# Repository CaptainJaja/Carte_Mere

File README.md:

# Carte mère – Coupe de France de Robotique

> Carte mère basée sur un **STM32H5** en boîtier **LQFP177**.  
> Conçue pour centraliser la communication et le pilotage des modules du robot, avec une connectique optimisée pour la robustesse et la modularité.

---

## Caractéristiques principales

- **Microcontrôleur** : STM32H5, LQFP177  
- **Interfaces série** : 12 UARTs, chacun exposé sur connecteurs **VCC – GND – TX – GND – RX** afin de permettre le torsadage avec un retour GND pour une meilleure intégrité du signal  
- **Bus I²C** : 3 bus indépendants, jusqu’à **13 connexions** possibles (chaque connecteur fournit 2 GPIOs, GND et 3V3)  
- **Convertisseurs analogiques (ADC)** : 12 entrées, rangées avec alimentation 3V3 et GND pour faciliter le câblage  
- **USB-C** : un connecteur intégré pour programmation et alimentation  
- **Timers** : 12 broches disponibles pour PWM et capture/compare  
- **GPIO** : 10 broches générales, chacune associée à GND et 3V3 pour plus de flexibilité  
- **SPI** : 4 full duplex master, avec chacun des broches power et deux gpios 

---

## Vues du PCB

### Face composants

### Face cuivre arrière

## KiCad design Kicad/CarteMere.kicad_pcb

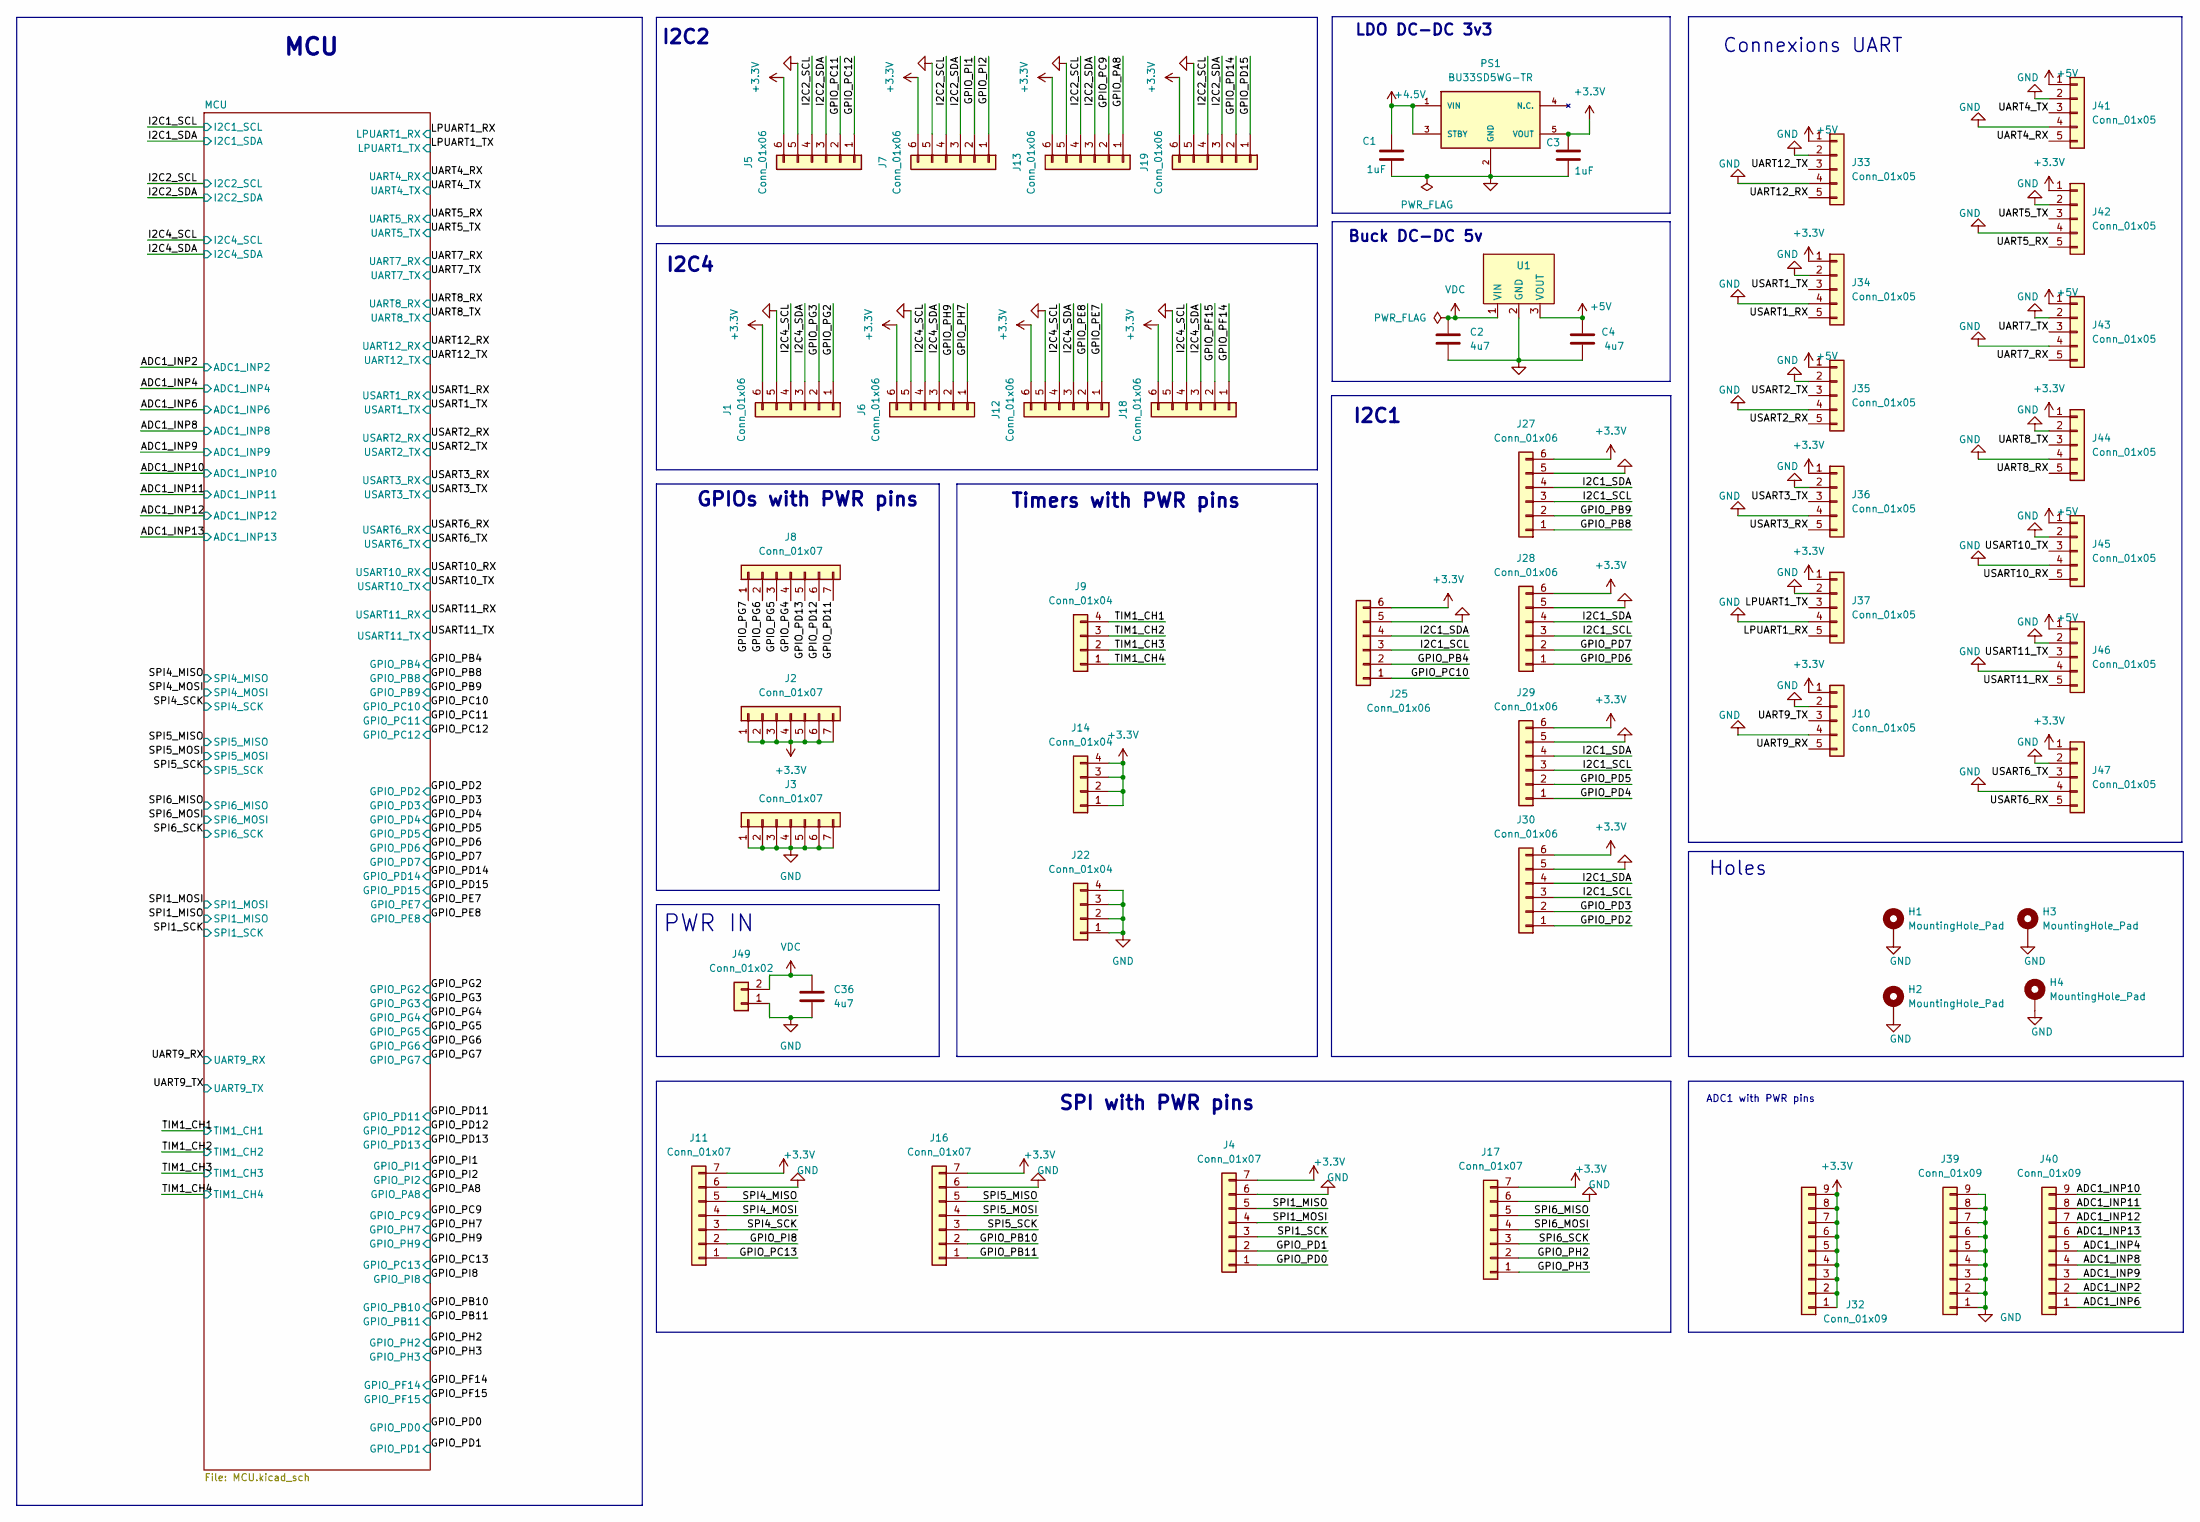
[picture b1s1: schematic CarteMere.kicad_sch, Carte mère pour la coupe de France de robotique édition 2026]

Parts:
C1, C3: 1uF; C_0603_1608Metric
C2: 4u7; C_1206_3216Metric
C4: 4u7; C_0603_1608Metric
C36: 4u7; C_0805_2012Metric
H1, H2, H3, H4: MountingHole_Pad; MountingHole_2.2mm_M2_Pad
J1, J5, J6, J7, J12, J13, J18, J19, J25, J27, J28, J29, J30: Conn_01x06; JST_EH_B6B-EH-A_1x06_P2.50mm_Vertical
J2, J3, J8: Conn_01x07; PinHeader_1x07_P2.54mm_Vertical
J4, J11, J16, J17: Conn_01x07; JST_EH_B7B-EH-A_1x07_P2.50mm_Vertical
J9, J14, J22: Conn_01x04; PinHeader_1x04_P2.54mm_Vertical
J10, J33, J34, J35, J36, J37, J41, J42, J43, J44, J45, J46, J47: Conn_01x05; JST_EH_B5B-EH-A_1x05_P2.50mm_Vertical
J32, J39, J40: Conn_01x09; PinHeader_1x09_P2.54mm_Vertical
J49: Conn_01x02; KF301-5.0-2P
PS1: BU33SD5WG-TR; SOT95P280X125-5N; Mouser_Part_Number 755-BU33SD5WG-TR
U1: StepDown3v3; MPN 173010x78

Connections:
+3.3V: C3.1, J1.6, J2.1, J2.2, J2.3, J2.4, J2.5, J2.6, J2.7, J4.7, J5.6, J6.6, J7.6, J10.1, J11.7, J12.6, J13.6, J14.1, J14.2, J14.3, J14.4, J16.7, J17.7, J18.6, J19.6, J25.6, J27.6, J28.6, J29.6, J30.6, J32.1, J32.2, J32.3, J32.4, J32.5, J32.6, J32.7, J32.8, J32.9, J34.1, J36.1, J37.1, J42.1, J44.1, J47.1, PS1.5 (VOUT); also elsewhere on the board
+4.5V: C1.1, PS1.1 (VIN), PS1.3 (STBY); also elsewhere on the board
+5V: C4.1, J33.1, J35.1, J41.1, J43.1, J45.1, J46.1, U1.3 (VOUT); also elsewhere on the board
/ADC1_INP2: J40.2; also elsewhere on the board
/ADC1_INP4: J40.5; also elsewhere on the board
/ADC1_INP6: J40.1; also elsewhere on the board
/ADC1_INP8: J40.4; also elsewhere on the board
/ADC1_INP9: J40.3; also elsewhere on the board
/ADC1_INP10: J40.9; also elsewhere on the board
/ADC1_INP11: J40.8; also elsewhere on the board
/ADC1_INP12: J40.7; also elsewhere on the board
/ADC1_INP13: J40.6; also elsewhere on the board
/GPIO_PA8: J13.1; also elsewhere on the board
/GPIO_PB4: J25.2; also elsewhere on the board
/GPIO_PB8: J27.1; also elsewhere on the board
/GPIO_PB9: J27.2; also elsewhere on the board
/GPIO_PB10: J16.2; also elsewhere on the board
/GPIO_PB11: J16.1; also elsewhere on the board
/GPIO_PC9: J13.2; also elsewhere on the board
/GPIO_PC10: J25.1; also elsewhere on the board
/GPIO_PC11: J5.2; also elsewhere on the board
/GPIO_PC12: J5.1; also elsewhere on the board
/GPIO_PC13: J11.1; also elsewhere on the board
/GPIO_PD0: J4.1; also elsewhere on the board
/GPIO_PD1: J4.2; also elsewhere on the board
/GPIO_PD2: J30.1; also elsewhere on the board
/GPIO_PD3: J30.2; also elsewhere on the board
/GPIO_PD4: J29.1; also elsewhere on the board
/GPIO_PD5: J29.2; also elsewhere on the board
/GPIO_PD6: J28.1; also elsewhere on the board
/GPIO_PD7: J28.2; also elsewhere on the board
/GPIO_PD11: J8.7; also elsewhere on the board
/GPIO_PD12: J8.6; also elsewhere on the board
/GPIO_PD13: J8.5; also elsewhere on the board
/GPIO_PD14: J19.2; also elsewhere on the board
/GPIO_PD15: J19.1; also elsewhere on the board
/GPIO_PE7: J12.1; also elsewhere on the board
/GPIO_PE8: J12.2; also elsewhere on the board
/GPIO_PF14: J18.1; also elsewhere on the board
/GPIO_PF15: J18.2; also elsewhere on the board
/GPIO_PG2: J1.1; also elsewhere on the board
/GPIO_PG3: J1.2; also elsewhere on the board
/GPIO_PG4: J8.4; also elsewhere on the board
/GPIO_PG5: J8.3; also elsewhere on the board
/GPIO_PG6: J8.2; also elsewhere on the board
/GPIO_PG7: J8.1; also elsewhere on the board
/GPIO_PH2: J17.2; also elsewhere on the board
/GPIO_PH3: J17.1; also elsewhere on the board
/GPIO_PH7: J6.1; also elsewhere on the board
/GPIO_PH9: J6.2; also elsewhere on the board
/GPIO_PI1: J7.2; also elsewhere on the board
/GPIO_PI2: J7.1; also elsewhere on the board
/GPIO_PI8: J11.2; also elsewhere on the board
/I2C1_SCL: J25.3, J27.3, J28.3, J29.3, J30.3; also elsewhere on the board
/I2C1_SDA: J25.4, J27.4, J28.4, J29.4, J30.4; also elsewhere on the board
/I2C2_SCL: J5.4, J7.4, J13.4, J19.4; also elsewhere on the board
/I2C2_SDA: J5.3, J7.3, J13.3, J19.3; also elsewhere on the board
/I2C4_SCL: J1.4, J6.4, J12.4, J18.4; also elsewhere on the board
/I2C4_SDA: J1.3, J6.3, J12.3, J18.3; also elsewhere on the board
/LPUART1_RX: J37.5; also elsewhere on the board
/LPUART1_TX: J37.3; also elsewhere on the board
/SPI1_MISO: J4.5; also elsewhere on the board
/SPI1_MOSI: J4.4; also elsewhere on the board
/SPI1_SCK: J4.3; also elsewhere on the board
/SPI4_MISO: J11.5; also elsewhere on the board
/SPI4_MOSI: J11.4; also elsewhere on the board
/SPI4_SCK: J11.3; also elsewhere on the board
/SPI5_MISO: J16.5; also elsewhere on the board
/SPI5_MOSI: J16.4; also elsewhere on the board
/SPI5_SCK: J16.3; also elsewhere on the board
/SPI6_MISO: J17.5; also elsewhere on the board
/SPI6_MOSI: J17.4; also elsewhere on the board
/SPI6_SCK: J17.3; also elsewhere on the board
/TIM1_CH1: J9.4; also elsewhere on the board
/TIM1_CH2: J9.3; also elsewhere on the board
/TIM1_CH3: J9.2; also elsewhere on the board
/TIM1_CH4: J9.1; also elsewhere on the board
/UART4_RX: J41.5; also elsewhere on the board
/UART4_TX: J41.3; also elsewhere on the board
/UART5_RX: J42.5; also elsewhere on the board
/UART5_TX: J42.3; also elsewhere on the board
/UART7_RX: J43.5; also elsewhere on the board
/UART7_TX: J43.3; also elsewhere on the board
/UART8_RX: J44.5; also elsewhere on the board
/UART8_TX: J44.3; also elsewhere on the board
/UART9_RX: J10.5; also elsewhere on the board
/UART9_TX: J10.3; also elsewhere on the board
/UART12_RX: J33.5; also elsewhere on the board
/UART12_TX: J33.3; also elsewhere on the board
/USART1_RX: J34.5; also elsewhere on the board
/USART1_TX: J34.3; also elsewhere on the board
/USART2_RX: J35.5; also elsewhere on the board
/USART2_TX: J35.3; also elsewhere on the board
/USART3_RX: J36.5; also elsewhere on the board
/USART3_TX: J36.3; also elsewhere on the board
/USART6_RX: J47.5; also elsewhere on the board
/USART6_TX: J47.3; also elsewhere on the board
/USART10_RX: J45.5; also elsewhere on the board
/USART10_TX: J45.3; also elsewhere on the board
/USART11_RX: J46.5; also elsewhere on the board
/USART11_TX: J46.3; also elsewhere on the board
GND: C1.2, C2.2, C3.2, C4.2, C36.2, H1.1, H2.1, H3.1, H4.1, J1.5, J3.1, J3.2, J3.3, J3.4, J3.5, J3.6, J3.7, J4.6, J5.5, J6.5, J7.5, J10.2, J10.4, J11.6, J12.5, J13.5, J16.6, J17.6, J18.5, J19.5, J22.1, J22.2, J22.3, J22.4, J25.5, J27.5, J28.5, J29.5, J30.5, J33.2, J33.4, J34.2, J34.4, J35.2, J35.4, J36.2, J36.4, J37.2, J37.4, J39.1, J39.2, J39.3, J39.4, J39.5, J39.6, J39.7, J39.8, J39.9, J41.2, J41.4, J42.2, J42.4, J43.2, J43.4, J44.2, J44.4, J45.2, J45.4, J46.2, J46.4, J47.2, J47.4, J49.1, PS1.2 (GND), U1.2 (GND); also elsewhere on the board
VDC: C2.1, C36.1, J49.2, U1.1 (VIN)

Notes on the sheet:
SPI with PWR pins
I2C2
MCU
PWR IN
I2C4
Connexions UART
Buck DC-DC 5v
LDO DC-DC 3v3
GPIOs with PWR pins
Timers with PWR pins
I2C1
ADC1 with PWR pins
Holes

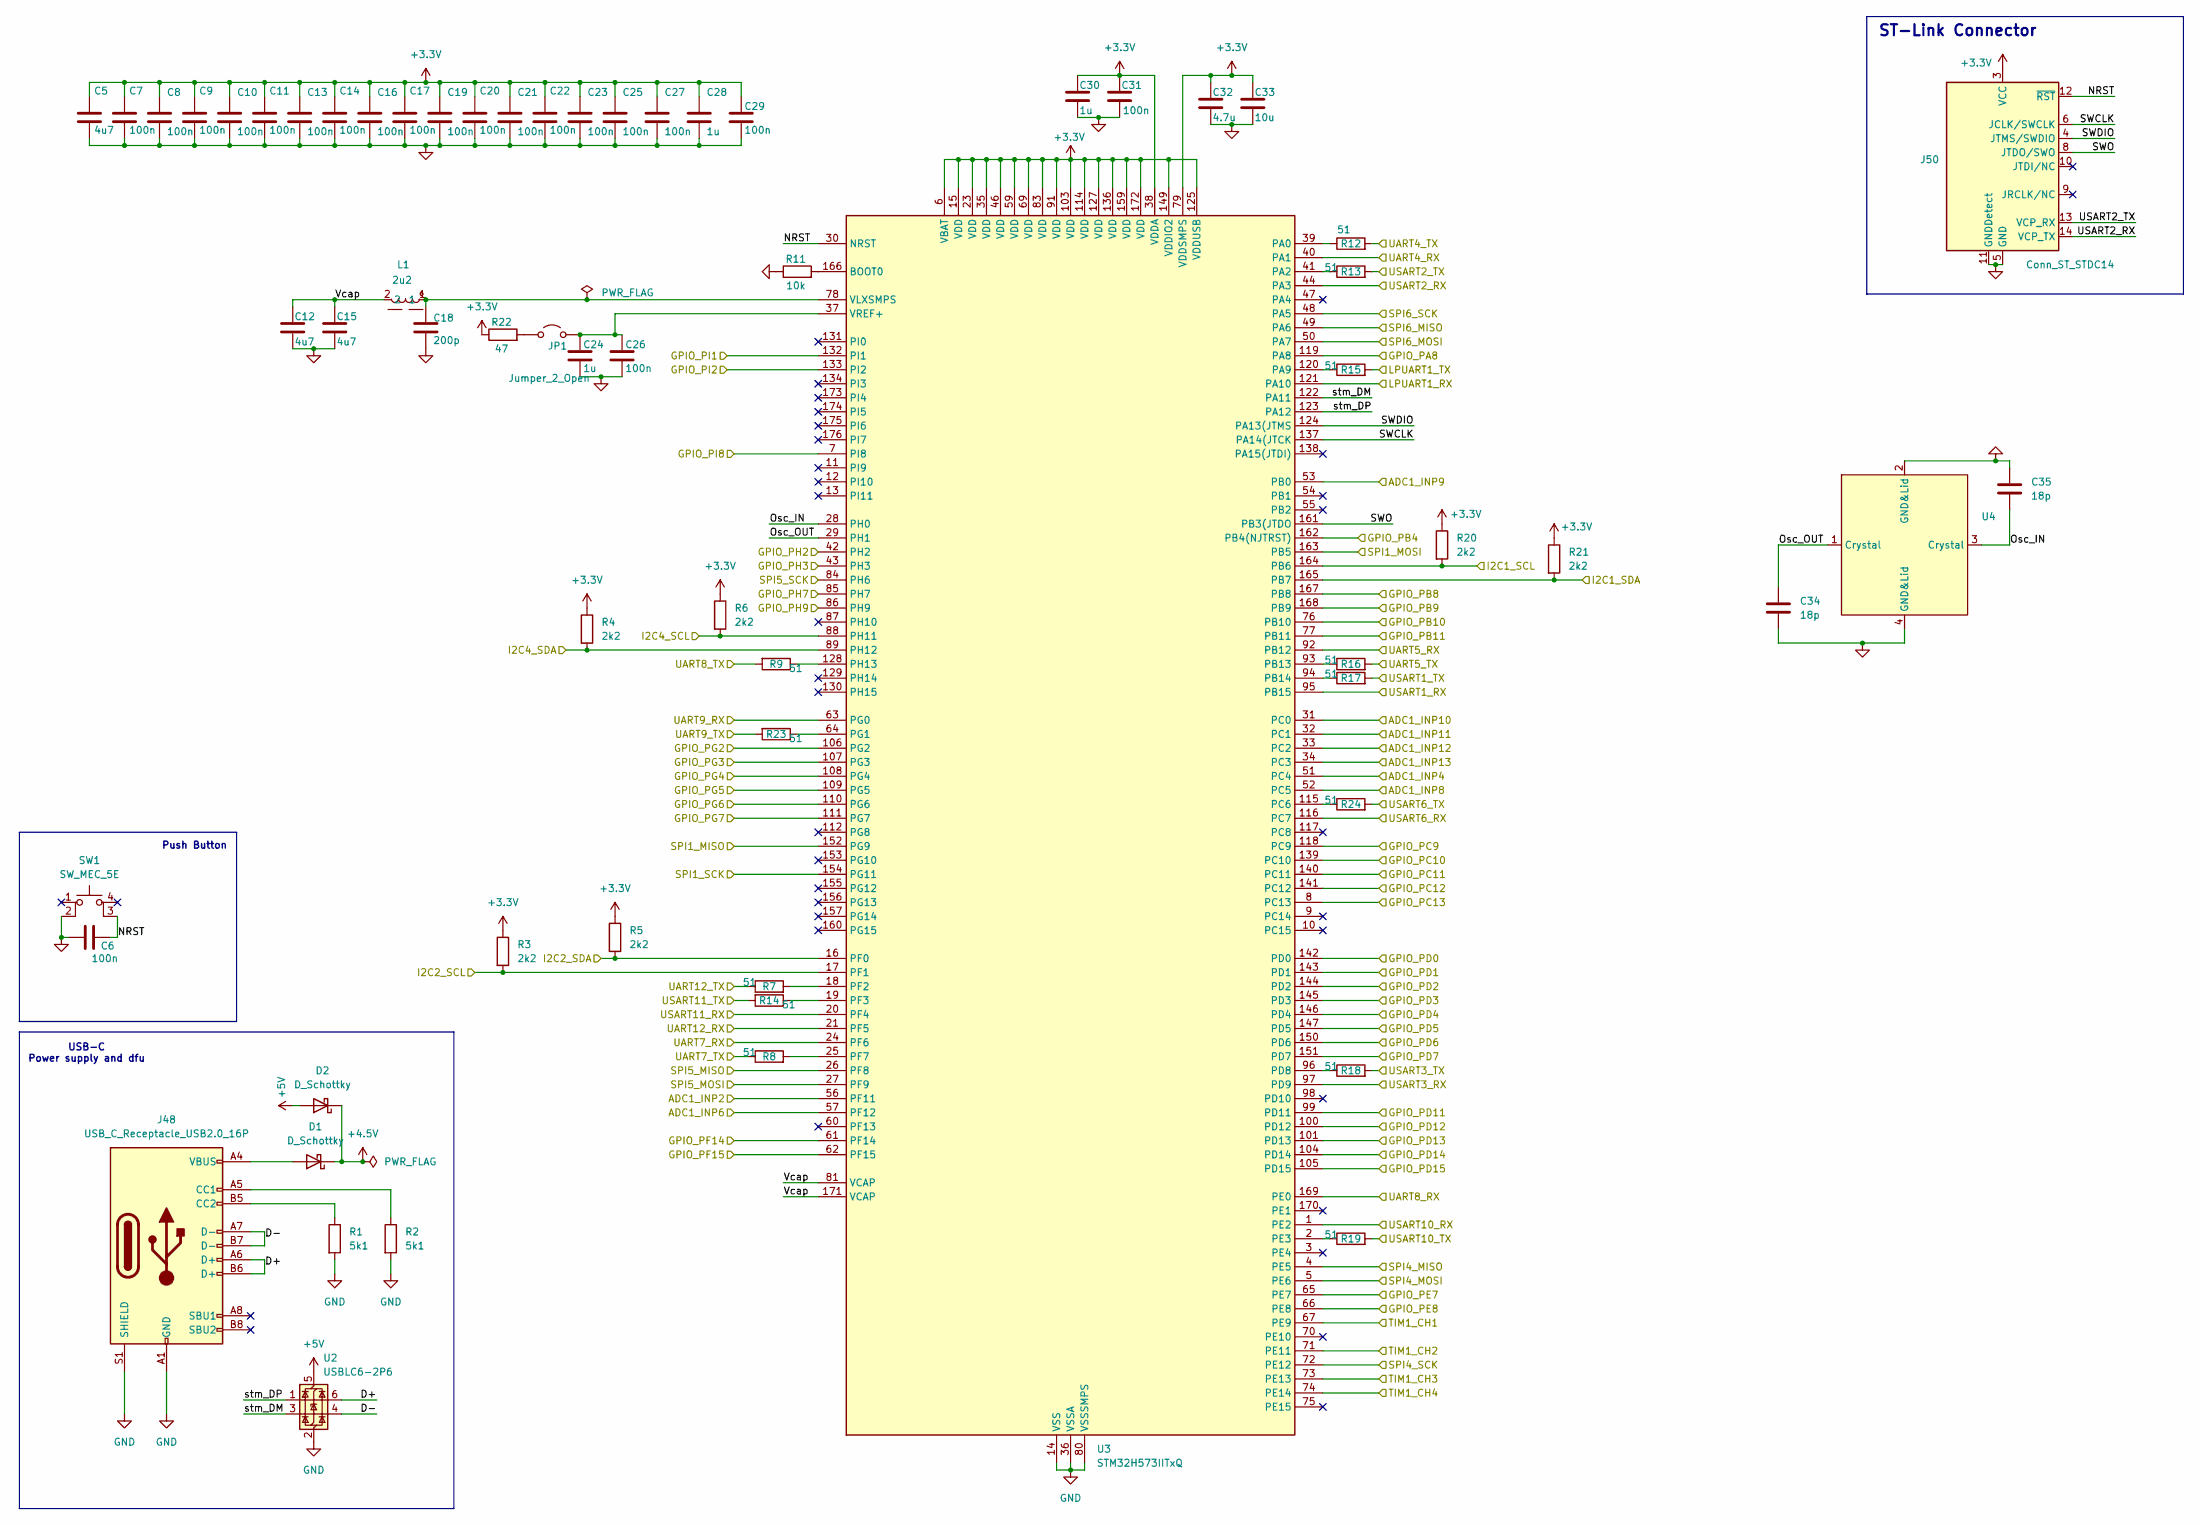
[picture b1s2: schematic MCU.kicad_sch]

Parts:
C5, C12, C15: 4u7; C_0402_1005Metric
C6, C7, C8, C9, C10, C11, C13, C14, C16, C17, C19, C20, C21, C22, C23, C25, C26, C27, C29, C31: 100n; C_0402_1005Metric
C18: 200p; C_0402_1005Metric
C24, C28, C30: 1u; C_0402_1005Metric
C32: 4.7u; C_0402_1005Metric
C33: 10u; C_0402_1005Metric
C34, C35: 18p; C_0603_1608Metric
D1, D2: D_Schottky; D_SMA
J48: USB_C_Receptacle_USB2.0_16P; USB_C_Receptacle_HRO_TYPE-C-31-M-12
J50: Conn_ST_STDC14; PinHeader_2x07_P1.27mm_Vertical_SMD
JP1: Jumper_2_Open; PinHeader_1x02_P2.54mm_Vertical
L1: 2u2; 7440660022
R1, R2: 5k1; R_0402_1005Metric
R3, R4, R5, R6, R20, R21: 2k2; R_0402_1005Metric
R7, R8, R9, R12, R13, R14, R15, R16, R17, R18, R19, R23, R24: 51; R_0402_1005Metric
R11: 10k; R_0402_1005Metric
R22: 47; R_0402_1005Metric
SW1: SW_MEC_5E; WS-TASU SMT Tact Switch 4.7x3.5 mm side push
U2: USBLC6-2P6; SOT-666
U3: STM32H573IITxQ; LQFP-176_24x24mm_P0.5mm
U4: WE-XTAL Quartz Crystal 8MHz

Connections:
+3.3V: C5.1, C7.1, C8.1, C9.1, C10.1, C11.1, C13.1, C14.1, C16.1, C17.1, C19.1, C20.1, C21.1, C22.1, C23.1, C25.1, C27.1, C28.1, C29.1, C30.1, C31.1, C32.1, C33.1, J50.3 (VCC), R3.1, R4.1, R5.1, R6.1, R20.1, R21.1, R22.1, U3.6 (VBAT), U3.15 (VDD), U3.23 (VDD), U3.35 (VDD), U3.38 (VDDA), U3.46 (VDD), U3.59 (VDD), U3.69 (VDD), U3.79 (VDDSMPS), U3.83 (VDD), U3.91 (VDD), U3.103 (VDD), U3.114 (VDD), U3.125 (VDDUSB), U3.127 (VDD), U3.136 (VDD), U3.149 (VDDIO2), U3.159 (VDD), U3.172 (VDD); also elsewhere on the board
+4.5V: D1.1 (K), D2.1 (K); also elsewhere on the board
+5V: D2.2 (A), U2.5 (VBUS); also elsewhere on the board
/ADC1_INP2: U3.56 (PF11); also elsewhere on the board
/ADC1_INP4: U3.51 (PC4); also elsewhere on the board
/ADC1_INP6: U3.57 (PF12); also elsewhere on the board
/ADC1_INP8: U3.52 (PC5); also elsewhere on the board
/ADC1_INP9: U3.53 (PB0); also elsewhere on the board
/ADC1_INP10: U3.31 (PC0); also elsewhere on the board
/ADC1_INP11: U3.32 (PC1); also elsewhere on the board
/ADC1_INP12: U3.33 (PC2); also elsewhere on the board
/ADC1_INP13: U3.34 (PC3); also elsewhere on the board
/GPIO_PA8: U3.119 (PA8); also elsewhere on the board
/GPIO_PB4: U3.162 (PB4(NJTRST)); also elsewhere on the board
/GPIO_PB8: U3.167 (PB8); also elsewhere on the board
/GPIO_PB9: U3.168 (PB9); also elsewhere on the board
/GPIO_PB10: U3.76 (PB10); also elsewhere on the board
/GPIO_PB11: U3.77 (PB11); also elsewhere on the board
/GPIO_PC9: U3.118 (PC9); also elsewhere on the board
/GPIO_PC10: U3.139 (PC10); also elsewhere on the board
/GPIO_PC11: U3.140 (PC11); also elsewhere on the board
/GPIO_PC12: U3.141 (PC12); also elsewhere on the board
/GPIO_PC13: U3.8 (PC13); also elsewhere on the board
/GPIO_PD0: U3.142 (PD0); also elsewhere on the board
/GPIO_PD1: U3.143 (PD1); also elsewhere on the board
/GPIO_PD2: U3.144 (PD2); also elsewhere on the board
/GPIO_PD3: U3.145 (PD3); also elsewhere on the board
/GPIO_PD4: U3.146 (PD4); also elsewhere on the board
/GPIO_PD5: U3.147 (PD5); also elsewhere on the board
/GPIO_PD6: U3.150 (PD6); also elsewhere on the board
/GPIO_PD7: U3.151 (PD7); also elsewhere on the board
/GPIO_PD11: U3.99 (PD11); also elsewhere on the board
/GPIO_PD12: U3.100 (PD12); also elsewhere on the board
/GPIO_PD13: U3.101 (PD13); also elsewhere on the board
/GPIO_PD14: U3.104 (PD14); also elsewhere on the board
/GPIO_PD15: U3.105 (PD15); also elsewhere on the board
/GPIO_PE7: U3.65 (PE7); also elsewhere on the board
/GPIO_PE8: U3.66 (PE8); also elsewhere on the board
/GPIO_PF14: U3.61 (PF14); also elsewhere on the board
/GPIO_PF15: U3.62 (PF15); also elsewhere on the board
/GPIO_PG2: U3.106 (PG2); also elsewhere on the board
/GPIO_PG3: U3.107 (PG3); also elsewhere on the board
/GPIO_PG4: U3.108 (PG4); also elsewhere on the board
/GPIO_PG5: U3.109 (PG5); also elsewhere on the board
/GPIO_PG6: U3.110 (PG6); also elsewhere on the board
/GPIO_PG7: U3.111 (PG7); also elsewhere on the board
/GPIO_PH2: U3.42 (PH2); also elsewhere on the board
/GPIO_PH3: U3.43 (PH3); also elsewhere on the board
/GPIO_PH7: U3.85 (PH7); also elsewhere on the board
/GPIO_PH9: U3.86 (PH9); also elsewhere on the board
/GPIO_PI1: U3.132 (PI1); also elsewhere on the board
/GPIO_PI2: U3.133 (PI2); also elsewhere on the board
/GPIO_PI8: U3.7 (PI8); also elsewhere on the board
/I2C1_SCL: R20.2, U3.164 (PB6); also elsewhere on the board
/I2C1_SDA: R21.2, U3.165 (PB7); also elsewhere on the board
/I2C2_SCL: R3.2, U3.17 (PF1); also elsewhere on the board
/I2C2_SDA: R5.2, U3.16 (PF0); also elsewhere on the board
/I2C4_SCL: R6.2, U3.88 (PH11); also elsewhere on the board
/I2C4_SDA: R4.2, U3.89 (PH12); also elsewhere on the board
/LPUART1_RX: U3.121 (PA10); also elsewhere on the board
/LPUART1_TX: R15.2; also elsewhere on the board
/MCU/D+: J48.A6 (D+), J48.B6 (D+), U2.6 (I/O1)
/MCU/D-: J48.A7 (D-), J48.B7 (D-), U2.4 (I/O2)
/MCU/NRST: C6.2, J50.12 (~RST), SW1.3 (K), U3.30 (NRST)
/MCU/Osc_IN: C35.2, U3.28 (PH0), U4.3 (Crystal)
/MCU/Osc_OUT: C34.1, U3.29 (PH1), U4.1 (Crystal)
/MCU/SWCLK: J50.6 (JCLK/SWCLK), U3.137 (PA14(JTCK)
/MCU/SWDIO: J50.4 (JTMS/SWDIO), U3.124 (PA13(JTMS)
/MCU/SWO: J50.8 (JTDO/SWO), U3.161 (PB3(JTDO)
/MCU/Vcap: C12.1, C15.1, L1.2, U3.81 (VCAP), U3.171 (VCAP)
/MCU/stm_DM: U2.3 (I/O2), U3.122 (PA11)
/MCU/stm_DP: U2.1 (I/O1), U3.123 (PA12)
/SPI1_MISO: U3.152 (PG9); also elsewhere on the board
/SPI1_MOSI: U3.163 (PB5); also elsewhere on the board
/SPI1_SCK: U3.154 (PG11); also elsewhere on the board
/SPI4_MISO: U3.4 (PE5); also elsewhere on the board
/SPI4_MOSI: U3.5 (PE6); also elsewhere on the board
/SPI4_SCK: U3.72 (PE12); also elsewhere on the board
/SPI5_MISO: U3.26 (PF8); also elsewhere on the board
/SPI5_MOSI: U3.27 (PF9); also elsewhere on the board
/SPI5_SCK: U3.84 (PH6); also elsewhere on the board
/SPI6_MISO: U3.49 (PA6); also elsewhere on the board
/SPI6_MOSI: U3.50 (PA7); also elsewhere on the board
/SPI6_SCK: U3.48 (PA5); also elsewhere on the board
/TIM1_CH1: U3.67 (PE9); also elsewhere on the board
/TIM1_CH2: U3.71 (PE11); also elsewhere on the board
/TIM1_CH3: U3.73 (PE13); also elsewhere on the board
/TIM1_CH4: U3.74 (PE14); also elsewhere on the board
/UART4_RX: U3.40 (PA1); also elsewhere on the board
/UART4_TX: R12.2; also elsewhere on the board
/UART5_RX: U3.92 (PB12); also elsewhere on the board
/UART5_TX: R16.2; also elsewhere on the board
/UART7_RX: U3.24 (PF6); also elsewhere on the board
/UART7_TX: R8.1; also elsewhere on the board
/UART8_RX: U3.169 (PE0); also elsewhere on the board
/UART8_TX: R9.2; also elsewhere on the board
/UART9_RX: U3.63 (PG0); also elsewhere on the board
/UART9_TX: R23.2; also elsewhere on the board
/UART12_RX: U3.21 (PF5); also elsewhere on the board
/UART12_TX: R7.1; also elsewhere on the board
/USART1_RX: U3.95 (PB15); also elsewhere on the board
/USART1_TX: R17.2; also elsewhere on the board
/USART2_RX: J50.14 (VCP_TX), U3.44 (PA3); also elsewhere on the board
/USART2_TX: J50.13 (VCP_RX), R13.2; also elsewhere on the board
/USART3_RX: U3.97 (PD9); also elsewhere on the board
/USART3_TX: R18.2; also elsewhere on the board
/USART6_RX: U3.116 (PC7); also elsewhere on the board
/USART6_TX: R24.2; also elsewhere on the board
/USART10_RX: U3.1 (PE2); also elsewhere on the board
/USART10_TX: R19.2; also elsewhere on the board
/USART11_RX: U3.20 (PF4); also elsewhere on the board
/USART11_TX: R14.2; also elsewhere on the board
GND: C5.2, C6.1, C7.2, C8.2, C9.2, C10.2, C11.2, C12.2, C13.2, C14.2, C15.2, C16.2, C17.2, C18.2, C19.2, C20.2, C21.2, C22.2, C23.2, C24.2, C25.2, C26.2, C27.2, C28.2, C29.2, C30.2, C31.2, C32.2, C33.2, C34.2, C35.1, J48.A1 (GND), J48.A12 (GND), J48.B1 (GND), J48.B12 (GND), J48.S1 (SHIELD), J50.5 (GND), J50.7 (GND), J50.11 (GNDDetect), R1.2, R2.2, R11.1, SW1.2, U2.2 (GND), U3.14 (VSS), U3.22 (VSS), U3.36 (VSSA), U3.45 (VSS), U3.58 (VSS), U3.68 (VSS), U3.80 (VSSSMPS), U3.82 (VSS), U3.90 (VSS), U3.102 (VSS), U3.113 (VSS), U3.126 (VSS), U3.135 (VSS), U3.148 (VSS), U3.158 (VSS), U4.2 (GND&Lid), U4.4 (GND&Lid); also elsewhere on the board
unnamed: D1.2 (A), J48.A4 (VBUS), J48.A9 (VBUS), J48.B4 (VBUS), J48.B9 (VBUS)
unnamed: J48.A5 (CC1), R2.1
unnamed: J48.B5 (CC2), R1.1
unnamed: JP1.1 (A), R22.2
unnamed: C24.1, C26.1, JP1.2 (B), U3.37 (VREF+)
unnamed: R11.2, U3.166 (BOOT0)
unnamed: R12.1, U3.39 (PA0)
unnamed: R13.1, U3.41 (PA2)
unnamed: R15.1, U3.120 (PA9)
unnamed: R16.1, U3.93 (PB13)
unnamed: R17.1, U3.94 (PB14)
unnamed: R24.1, U3.115 (PC6)
unnamed: R18.1, U3.96 (PD8)
unnamed: R19.1, U3.2 (PE3)
unnamed: R7.2, U3.18 (PF2)
unnamed: R14.1, U3.19 (PF3)
unnamed: R8.2, U3.25 (PF7)
unnamed: R23.1, U3.64 (PG1)
unnamed: R9.1, U3.128 (PH13)
unnamed: C18.1, L1.1, U3.78 (VLXSMPS)

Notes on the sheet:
USB-C Power supply and dfu
Push Button
ST-Link Connector

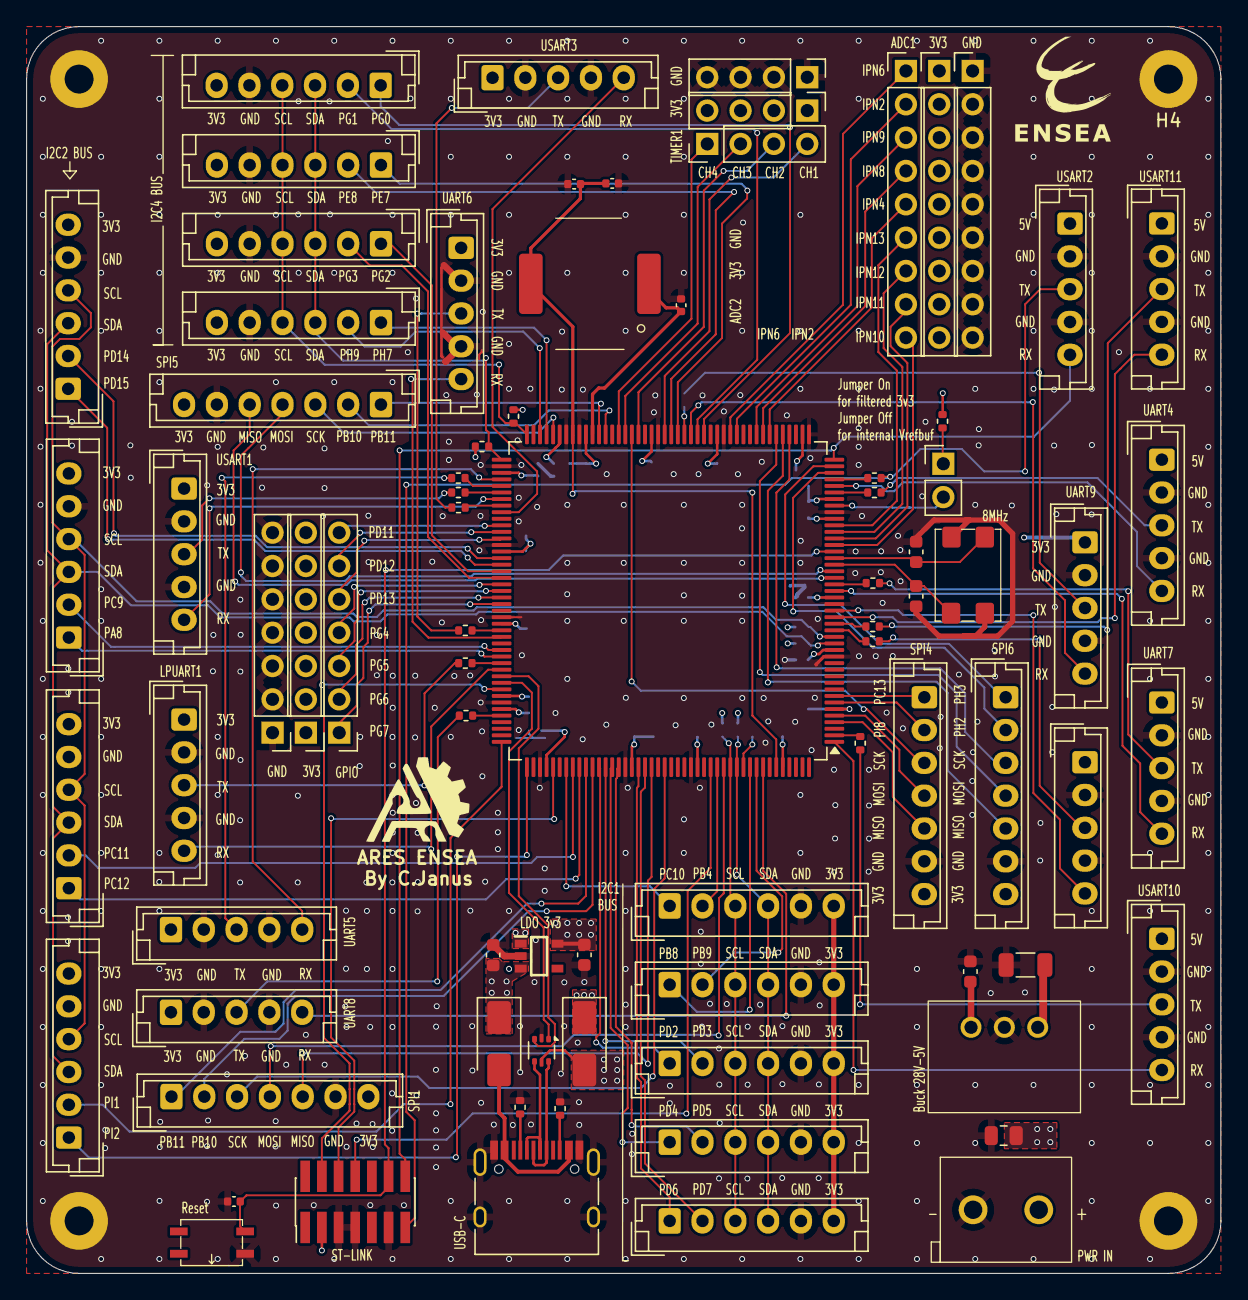
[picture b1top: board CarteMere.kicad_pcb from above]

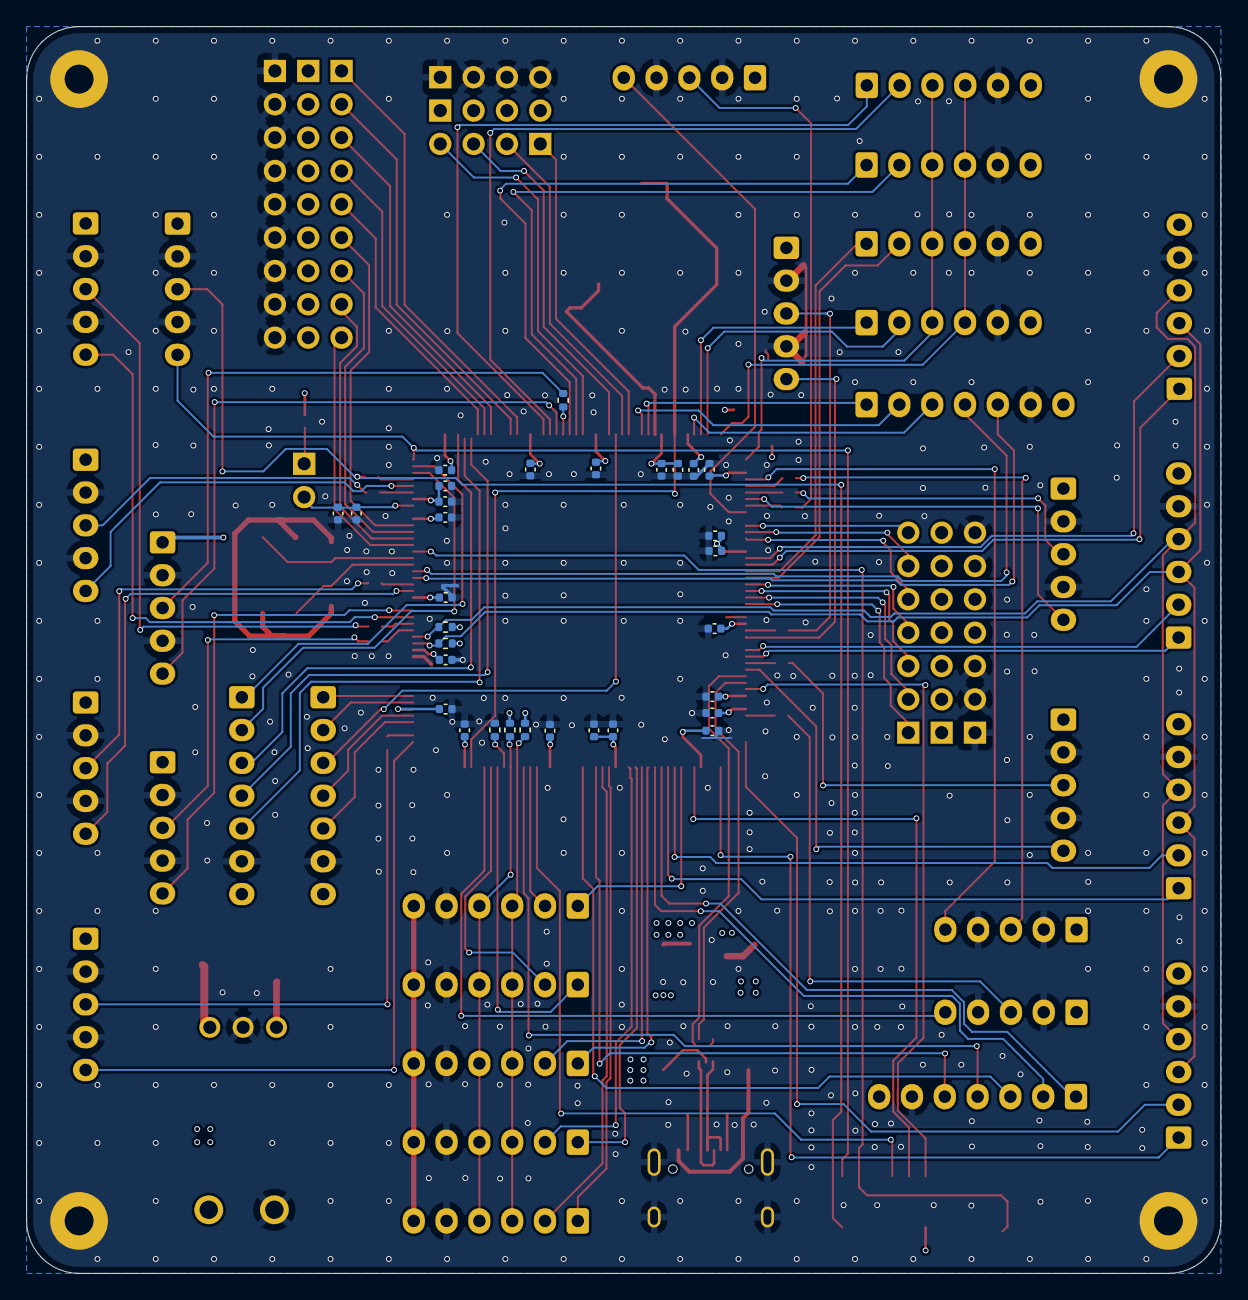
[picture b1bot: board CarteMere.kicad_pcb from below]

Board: 4 copper layers, 91.0 x 95.0 mm, 115 parts (31 on the bottom side), 134 nets.

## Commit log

2025-09-16 ajout du projet kicad carte mere
2025-09-16 ajout images du projet kicad carte mere
2025-09-19 maj README
2025-09-21 ajout spi et maj readme
2025-09-21 final push--ajout des vias
2025-09-23 ajout d'un connecteur SPI
